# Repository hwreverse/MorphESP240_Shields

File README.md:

# MorphESP240 Shields
Here I will publish finished and "Work-in Progress" Shields Designs for the MorphESP 240 by [@ccadic](https://github.com/ccadic).
The MorphESP 240 is available after a successful campaign [here on Crowdsupply](https://www.crowdsupply.com/morpheans/morphesp-240). 

<br><br>
NB: I don't supply the firmware, I am busy with electronics :))

### - [Gamepad Shield 3D](https://github.com/hwreverse/MorphESP240_Shields/tree/main/mesp240_3Dpad) (complete)(UPDATED : 21.Aug.2021!)

- Next evolution of the Gamepad Shield in a new design with two additional analog josticks and a I2C Gyroscope + Accelerometer integrated circuit for Position & Inertia capture. 
- 2x4 Button Gamepad Shield and connection to optional Buzzer ready to be fabricated and assembled by the PCBA service of your choice. It can also be soldered by hand as I used only 0805 and SOT-23 footprints for the passives and the transistor (on the backside).  Pushbuttons are classic, comfy 12mm x 12mm x 4.3/5mm units, that won't use that much your fingertips. 
 
- <b>UPDATED: Moved all parts to front side. Changed strategy to factory assemby, therefore changed all passives to mainly 0402, at max 0603. Changed Accelerometer + Gyro to MPU6050, the Alps thumb joysticks to 3D161 from Korean Hroparts Elec (what was available @ JLCPCB/Parts for PCBA). 
- Removed the stupid 5V Connection. Added hardware debounce with RC-lowpass & Schmitt-Trigger on all buttons. 
- Added connection to +3.3V vibration motor. Added 2 LEDs Added 4 Pads (GND, +3.3V, SDA, SCL) on the backside of the PCB to be able to connect independently with the I2C BUS (gyro)
- Gerber files, BOM and CPL Files for Assembly (JLCPCB Format) and Project archive (Kicad 5.99 nightly only Format!) are available too. 

New Model:</b>

Old photos:

### - [Gamepad Shield](https://github.com/hwreverse/MorphESP240_Shields/tree/main/mesp240_gamepadshield) (complete)

- 2x4 Button Gamepad Shield and connection to optional Buzzer ready to be fabricated and assembled by the PCBA service of your choice. It can also be soldered by hand as I used only 0805 and SOT-23 footprints for the passives and the transistor (on the backside).  Pushbuttons are classic, comfy 12mm x 12mm x 4.3/5mm units, that won't use that much your fingertips. 
- Gerber files and archive are available too. I included alsoa BOM and a CPL file in the main Directory in the [JLCPCB](https://jlcpcb.com/) Format for PCBA (PCB Assembly)

### - [IRMaster Shield](https://github.com/hwreverse/MorphESP240_Shields/tree/main/mesp240_irmaster) (complete)

- Let's you control all IR controllable appliances: TV's, AC units, set top boxes,... Can learn any IR Code (What are IR Receiver and MorphESP-240 power good for!) 
Has also a special "TV–π–soff!" Button, with a functionality borrowed from TV-B-Gone, which turn off any known TV!
- Gerber files and archive are available too. 

### - [OPLL 8-bit Sound Card Shield](https://github.com/hwreverse/MorphESP240_Shields/tree/main/mesp240_opll) (complete)

- OPLL 8-Bit Sound Card Shield based on the cheap Yamaha YM2413B Sound Chip. As the MorphESP-240 only has 3.3V from the Lipo (5V only from USB), we had to generate 5V through a Boost converter for the YM2413B as well as the opamp. This implied that level conversion had to be added as well. Special care was exercised to get rid of the ripples for the 5V rail.
- Gerber files and archive are available too. 

### - [Da Bomb Shield (Draft - unfinished)](https://github.com/hwreverse/MorphESP240_Shields/tree/main/da_bomb_breadboard)

- If the project is great, then the Prototyping Shield must be surely...

**- Da Bomb!**

*... in the early design stage ...*

### - [MorphESP 240 to Sharp PC-G850* Shield](https://github.com/hwreverse/MorphESP240_Shields/tree/main/morphesp240_g850_interface) (complete)

- This shield offers an interface with bidirectiional level shifting form the 11pin Interface of Sharp Vintage Pocket Computers of the PC-G850 Series. (and any other Sharp with a 11pin Connector)<br>
- This Project is ready to be fabricated, a zip of the Gerber files is included.. As usual, I included alsoa BOM and a CPL file in the main Directory in the [JLCPCB](https://jlcpcb.com/) Format for PCBA (PCB Assembly), so you don't have to solder those pesky 0402 Resistors and capacitors 
<br>For more Pocketcomputer hardware see my other repositories [here](https://hwreverse.github.io/)

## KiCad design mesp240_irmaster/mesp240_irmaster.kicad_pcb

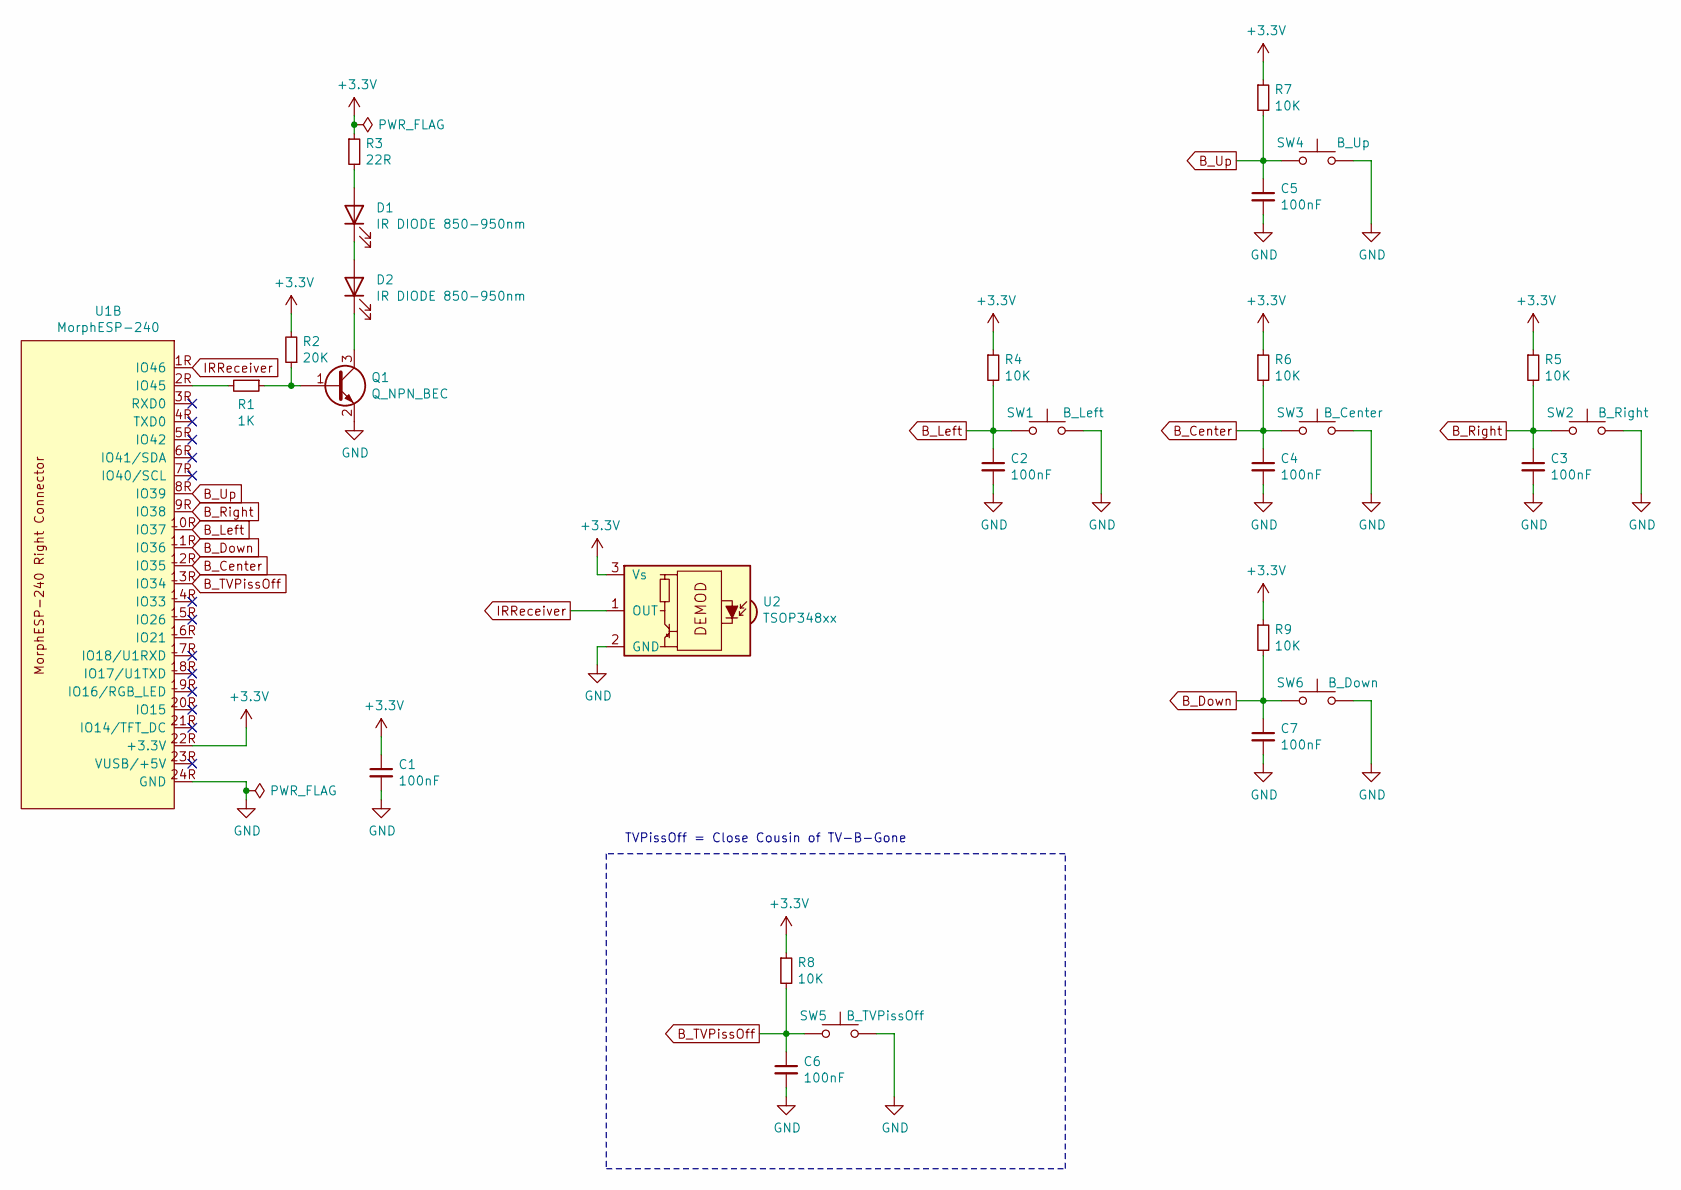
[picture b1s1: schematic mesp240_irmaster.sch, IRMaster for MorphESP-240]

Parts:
C1, C2, C3, C4, C5, C6, C7: 100nF; C_0805_2012Metric
D1: IR DIODE 850-950nm; LED_D5.0mm_IRBlack
D2: IR DIODE 850-950nm; LED_D5.0mm_IRGrey
Q1: Q_NPN_BEC; SOT-23
R1: 1K; R_0805_2012Metric_Pad1.20x1.40mm_HandSolder
R2: 20K; R_0805_2012Metric_Pad1.20x1.40mm_HandSolder
R3: 22R; R_0805_2012Metric_Pad1.20x1.40mm_HandSolder
R4, R5, R6, R7, R8, R9: 10K; R_0805_2012Metric_Pad1.20x1.40mm_HandSolder
SW1: B_Left; SW_PUSH_6mm_H4.3mm
SW2: B_Right; SW_PUSH_6mm_H4.3mm
SW3: B_Center; SW_PUSH_6mm_H4.3mm
SW4: B_Up; SW_PUSH_6mm_H4.3mm
SW5: B_TVPissOff; SW_PUSH_6mm_H4.3mm
SW6: B_Down; SW_PUSH_6mm_H4.3mm
U1: MorphESP-240; morphesp240
U2: TSOP348xx; Vishay_MOLD-3Pin

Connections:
+3V3: C1.1, R2.2, R3.1, R4.1, R5.1, R6.1, R7.1, R8.1, R9.1, U1.22R (+3.3V), U2.3 (Vs)
B_Center: C4.1, R6.2, SW3.1, U1.12R (IO35)
B_Down: C7.1, R9.2, SW6.1, U1.11R (IO36)
B_Left: C2.1, R4.2, SW1.1, U1.10R (IO37)
B_Right: C3.1, R5.2, SW2.1, U1.9R (IO38)
B_TVPissOff: C6.1, R8.2, SW5.1, U1.13R (IO34)
B_Up: C5.1, R7.2, SW4.1, U1.8R (IO39)
GND: C1.2, C2.2, C3.2, C4.2, C5.2, C6.2, C7.2, Q1.2 (E), SW1.2, SW2.2, SW3.2, SW4.2, SW5.2, SW6.2, U1.24R (GND), U2.2 (GND)
IRReceiver: U1.1R (IO46), U2.1 (OUT)
unnamed: D1.1 (K), D2.2 (A)
unnamed: D1.2 (A), R3.2
unnamed: D2.1 (K), Q1.3 (C)
unnamed: Q1.1 (B), R1.1, R2.1
unnamed: R1.2, U1.2R (IO45)

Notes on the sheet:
TVPissOff = Close Cousin of TV-B-Gone

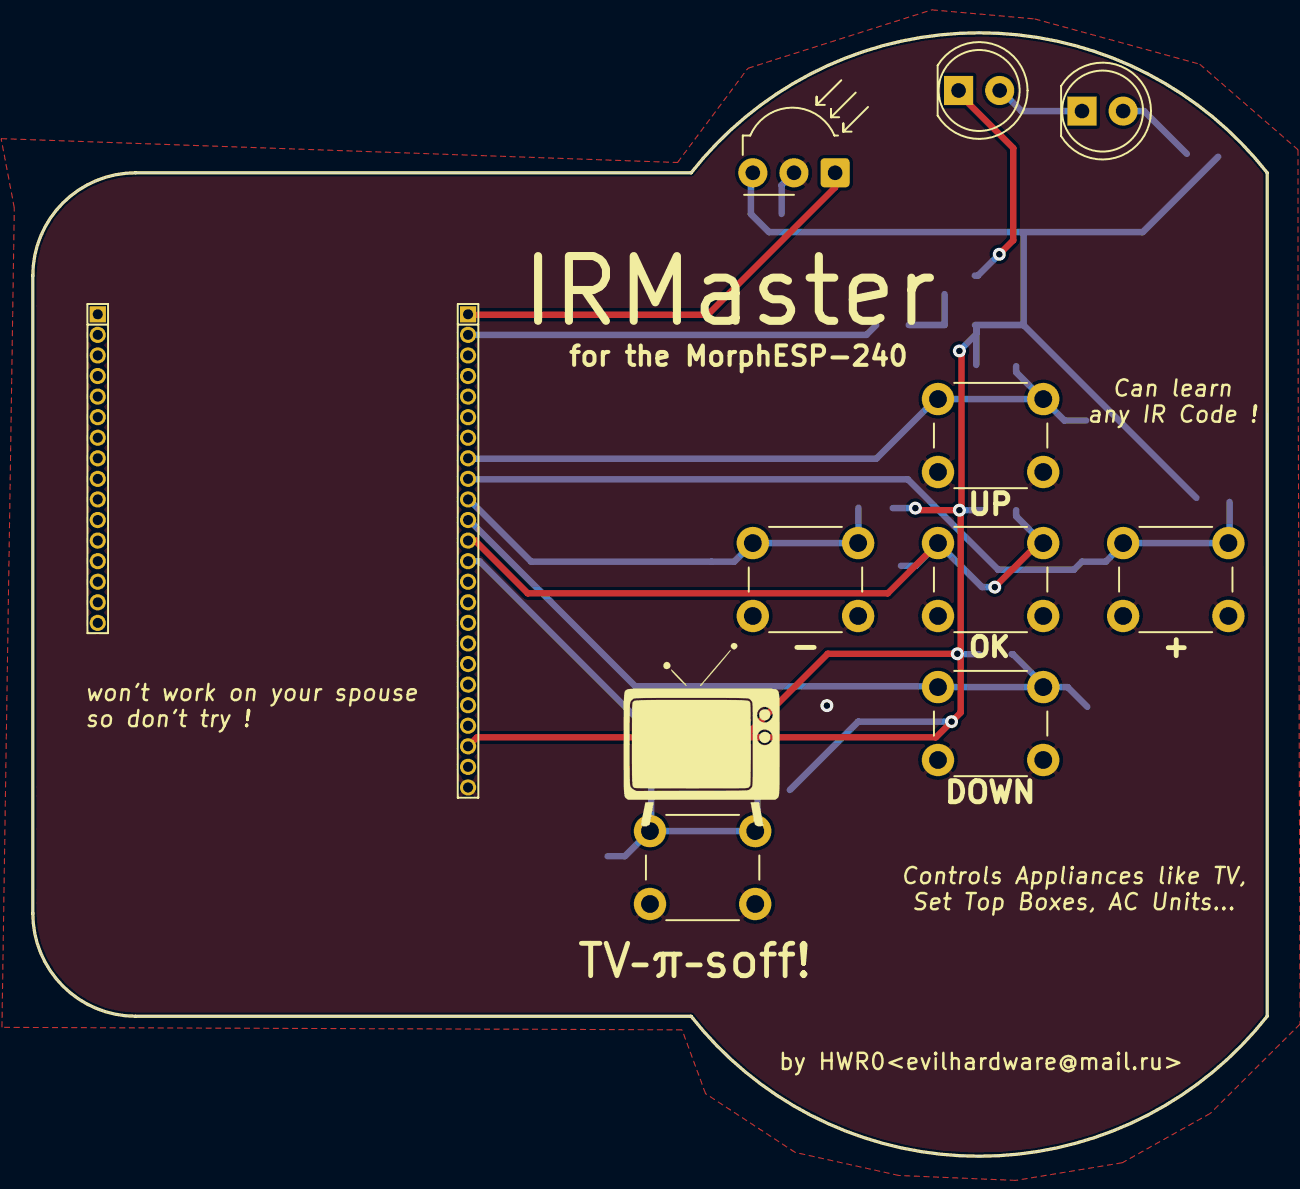
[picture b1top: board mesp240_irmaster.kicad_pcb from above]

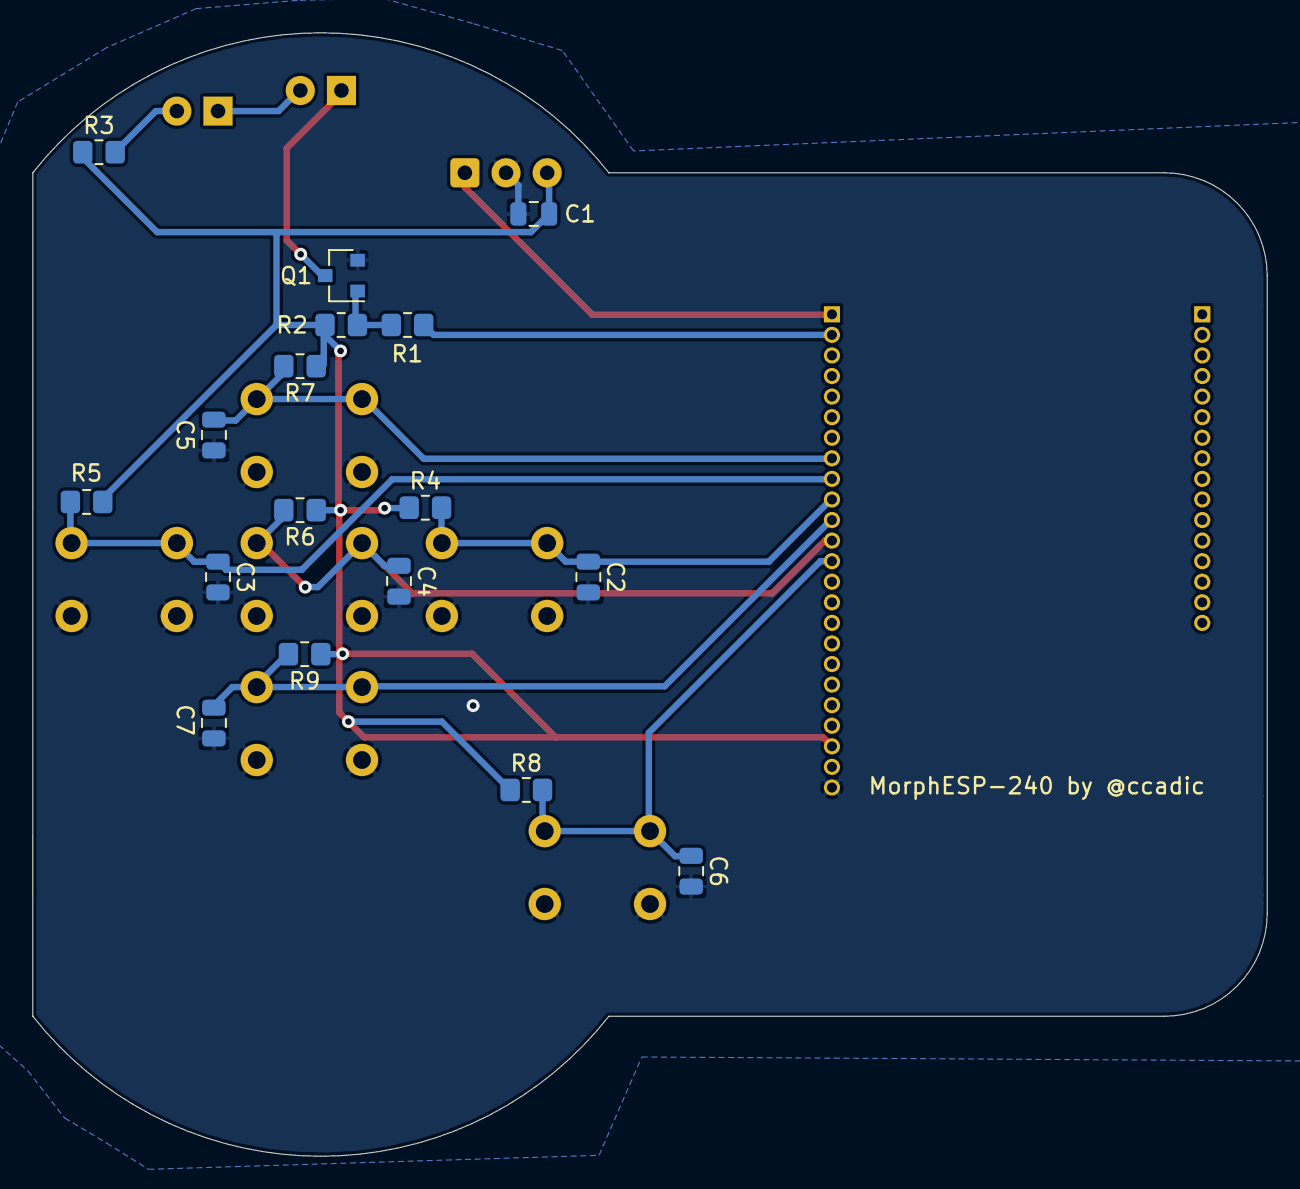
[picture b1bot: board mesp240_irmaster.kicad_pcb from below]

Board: 2 copper layers, 76.2 x 69.4 mm, 27 parts (17 on the bottom side), 14 nets.

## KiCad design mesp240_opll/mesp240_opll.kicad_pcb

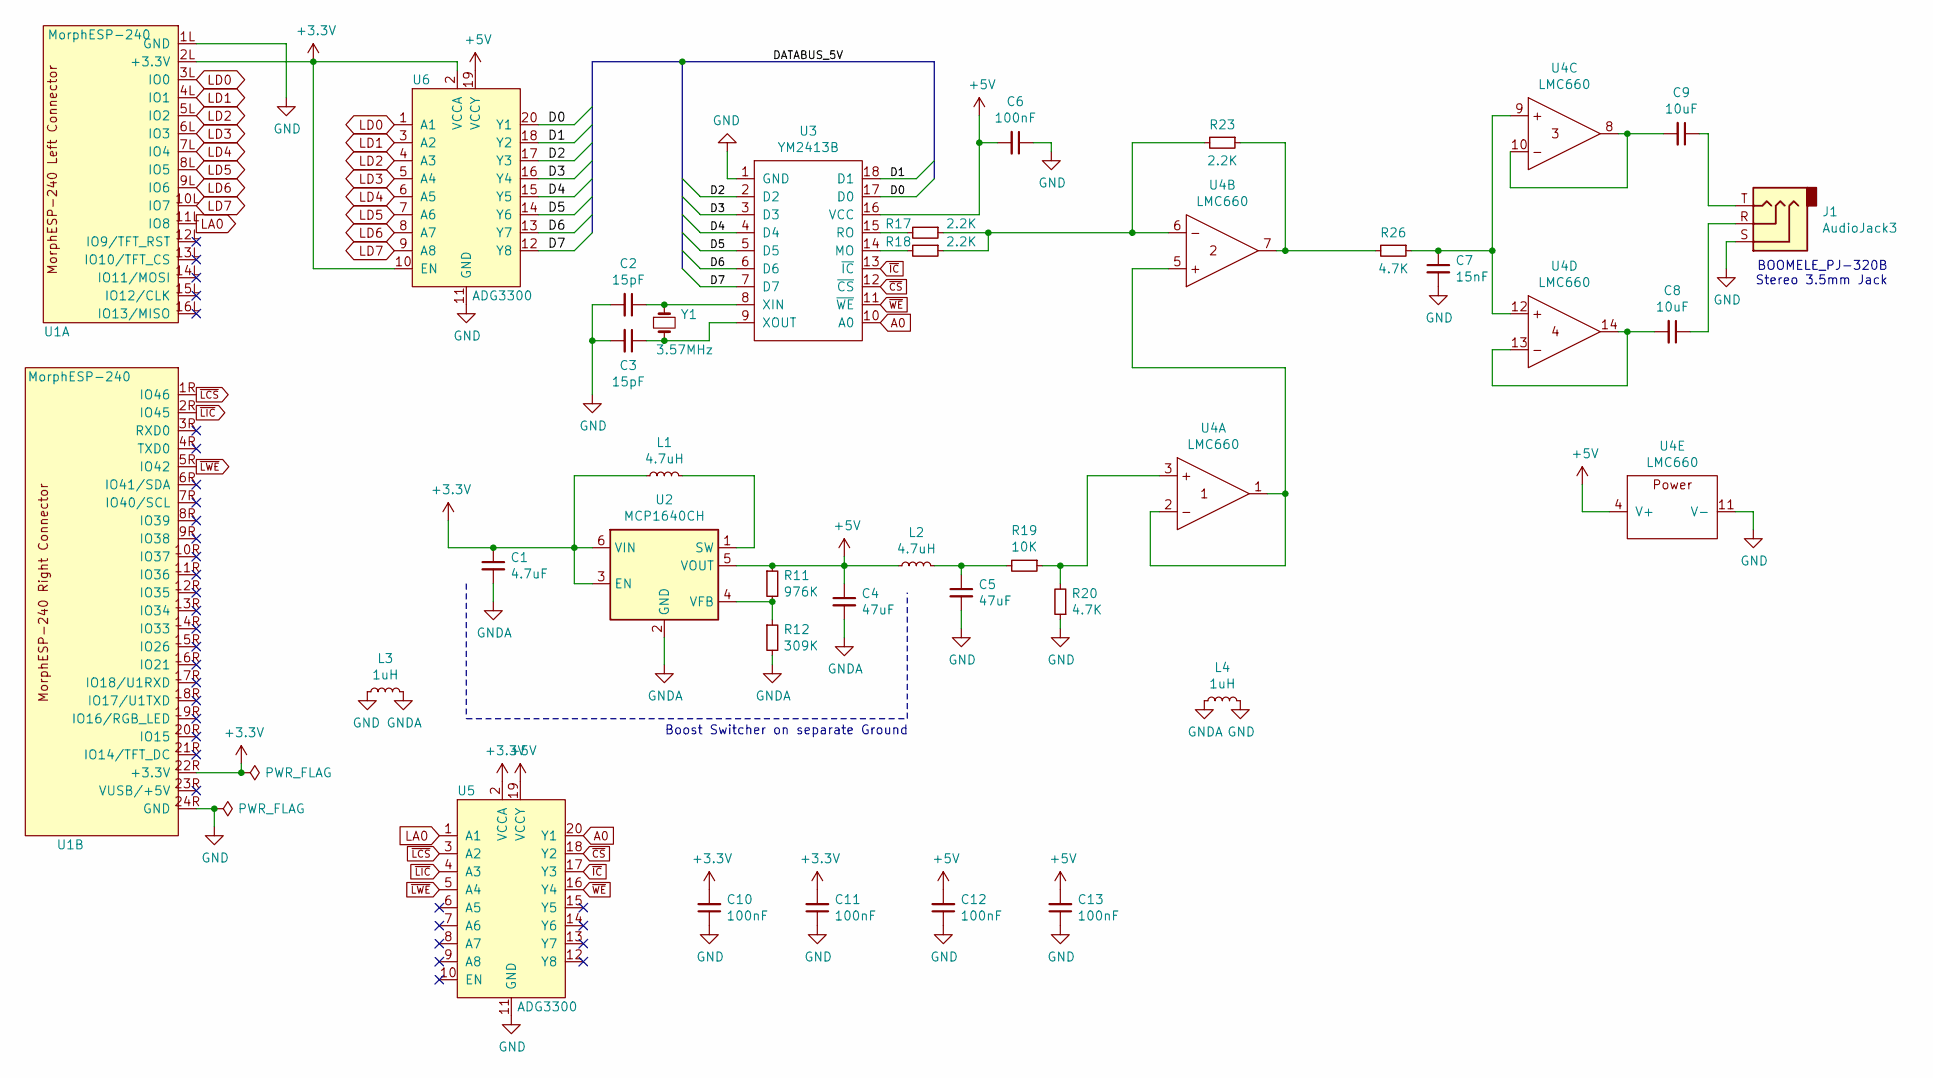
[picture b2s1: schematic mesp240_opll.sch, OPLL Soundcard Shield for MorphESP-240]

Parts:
C1: 4.7uF; C_0402_1005Metric
C2, C3: 15pF; C_0402_1005Metric
C4, C5: 47uF; C_1206_3216Metric_Pad1.33x1.80mm_HandSolder
C6, C10, C11, C12, C13: 100nF; C_0402_1005Metric
C7: 15nF; C_0402_1005Metric
C8, C9: 10uF; C_0805_2012Metric_Pad1.18x1.45mm_HandSolder
J1: AudioJack3; BOOMELE_PJ-320B
L1, L2: 4.7uH; C_1210_3225Metric_Pad1.33x2.70mm_HandSolder
L3, L4: 1uH; L_0805_2012Metric
R11: 976K; R_0402_1005Metric
R12: 309K; R_0402_1005Metric
R17, R18, R23: 2.2K; R_0603_1608Metric
R19: 10K; R_0603_1608Metric
R20, R26: 4.7K; R_0603_1608Metric
U1: MorphESP-240; morphesp240
U2: MCP1640CH; SOT-23-6
U3: YM2413B; DIP-18_W7.62mm
U4: LMC660; SOIC127P600X175-14N
U5, U6: ADG3300; TSSOP-20_4.4x6.5mm_P0.65mm
Y1: 3.57MHz; Crystal_SMD_3225-4Pin_3.2x2.5mm

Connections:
+3V3: C1.1, C10.2, C11.2, L1.1, U1.2L (+3.3V), U1.22R (+3.3V), U2.3 (EN), U2.6 (VIN), U5.2 (VCCA), U6.2 (VCCA), U6.10 (EN)
+5V: C4.1, C6.2, C12.2, C13.2, L2.1, R11.1, U2.5 (VOUT), U3.16 (VCC), U4.4 (V+), U5.19 (VCCY), U6.19 (VCCY)
/D0: U3.17 (D0), U6.20 (Y1)
/D1: U3.18 (D1), U6.18 (Y2)
/D2: U3.2 (D2), U6.17 (Y3)
/D3: U3.3 (D3), U6.16 (Y4)
/D4: U3.4 (D4), U6.15 (Y5)
/D5: U3.5 (D5), U6.14 (Y6)
/D6: U3.6 (D6), U6.13 (Y7)
/D7: U3.7 (D7), U6.12 (Y8)
A0: U3.10 (A0), U5.20 (Y1)
GND: C2.2, C3.2, C5.2, C6.1, C7.2, C10.1, C11.1, C12.1, C13.1, J1.S, L3.2, L4.2, R20.1, U1.1L (GND), U1.24R (GND), U3.1 (GND), U4.11 (V-), U5.11 (GND), U6.11 (GND)
GNDA: C1.2, C4.2, L3.1, L4.1, R12.2, U2.2 (GND)
LA0: U1.11L (IO8), U5.1 (A1)
LD0: U1.3L (IO0), U6.1 (A1)
LD1: U1.4L (IO1), U6.3 (A2)
LD2: U1.5L (IO2), U6.4 (A3)
LD3: U1.6L (IO3), U6.5 (A4)
LD4: U1.7L (IO4), U6.6 (A5)
LD5: U1.8L (IO5), U6.7 (A6)
LD6: U1.9L (IO6), U6.8 (A7)
LD7: U1.10L (IO7), U6.9 (A8)
unnamed: C2.1, U3.8 (XIN), Y1.1
unnamed: C3.1, U3.9 (XOUT), Y1.2
unnamed: C5.1, L2.2, R19.2
unnamed: C7.1, R26.1, U4.9, U4.12
unnamed: C8.1, J1.R
unnamed: C8.2, U4.13, U4.14
unnamed: C9.1, J1.T
unnamed: C9.2, U4.8, U4.10
unnamed: L1.2, U2.1 (SW)
unnamed: R11.2, R12.1, U2.4 (VFB)
unnamed: R17.1, R18.1, R23.2, U4.6
unnamed: R17.2, U3.15 (RO)
unnamed: R18.2, U3.14 (MO)
unnamed: R19.1, R20.2, U4.3
unnamed: R23.1, R26.2, U4.7
unnamed: U4.1, U4.2, U4.5
~CS: U3.12 (~CS), U5.18 (Y2)
~IC: U3.13 (~IC), U5.17 (Y3)
~LCS: U1.1R (IO46), U5.3 (A2)
~LIC: U1.2R (IO45), U5.4 (A3)
~LWE: U1.5R (IO42), U5.5 (A4)
~WE: U3.11 (~WE), U5.16 (Y4)

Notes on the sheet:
BOOMELE_PJ-320B Stereo 3.5mm Jack
Boost Switcher on separate Ground

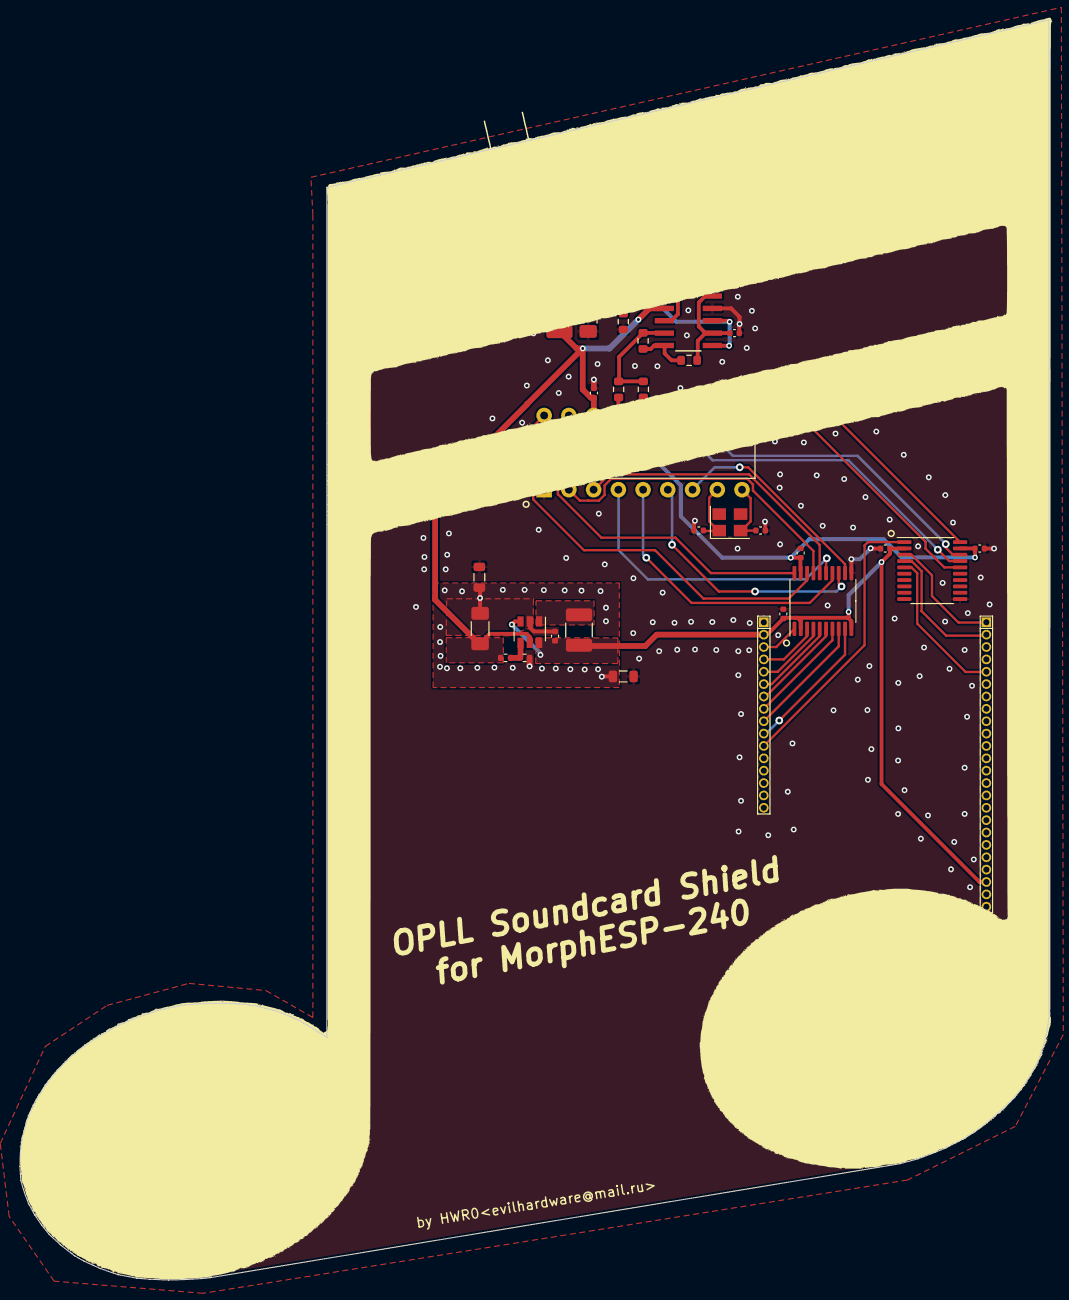
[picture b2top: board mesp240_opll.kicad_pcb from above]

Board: 2 copper layers, 105.7 x 129.4 mm, 33 parts (0 on the bottom side), 44 nets.

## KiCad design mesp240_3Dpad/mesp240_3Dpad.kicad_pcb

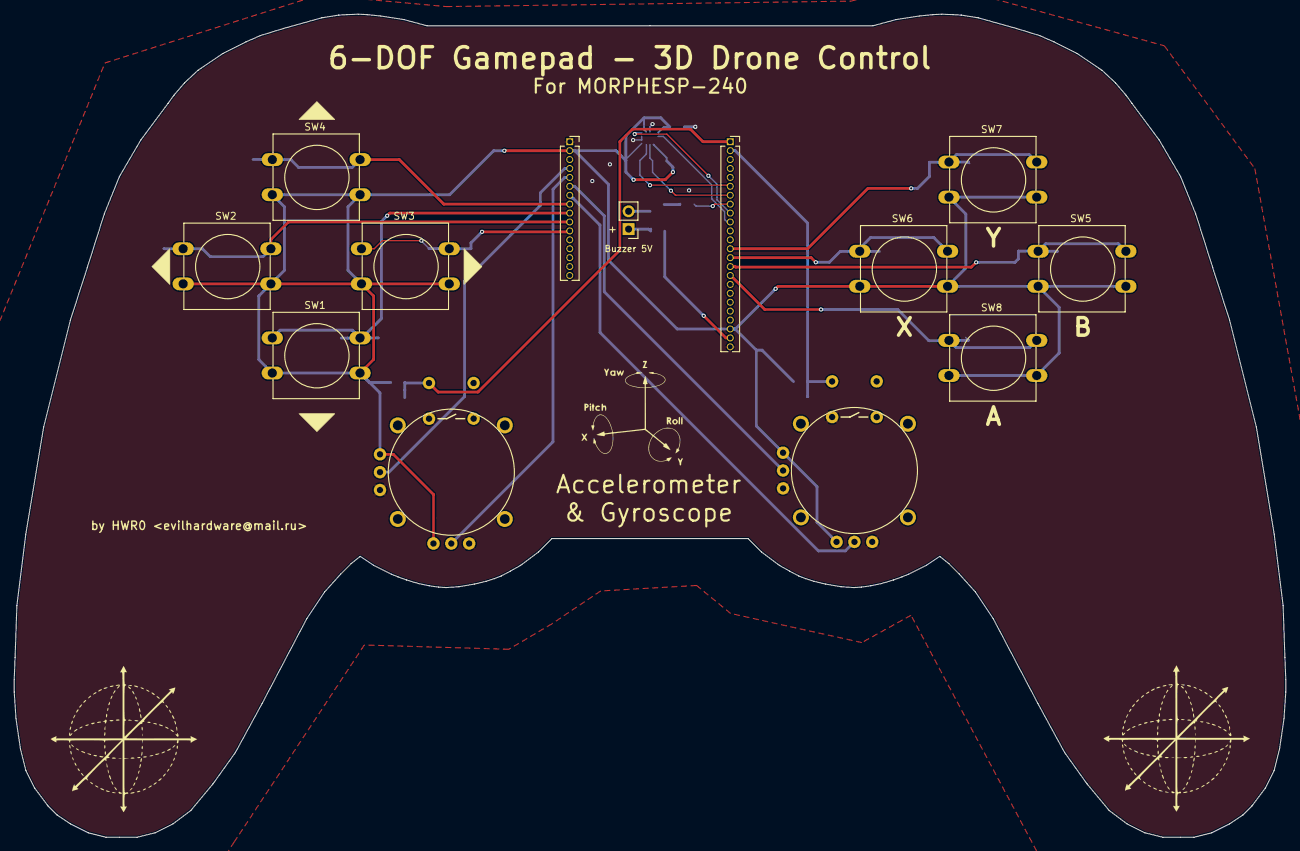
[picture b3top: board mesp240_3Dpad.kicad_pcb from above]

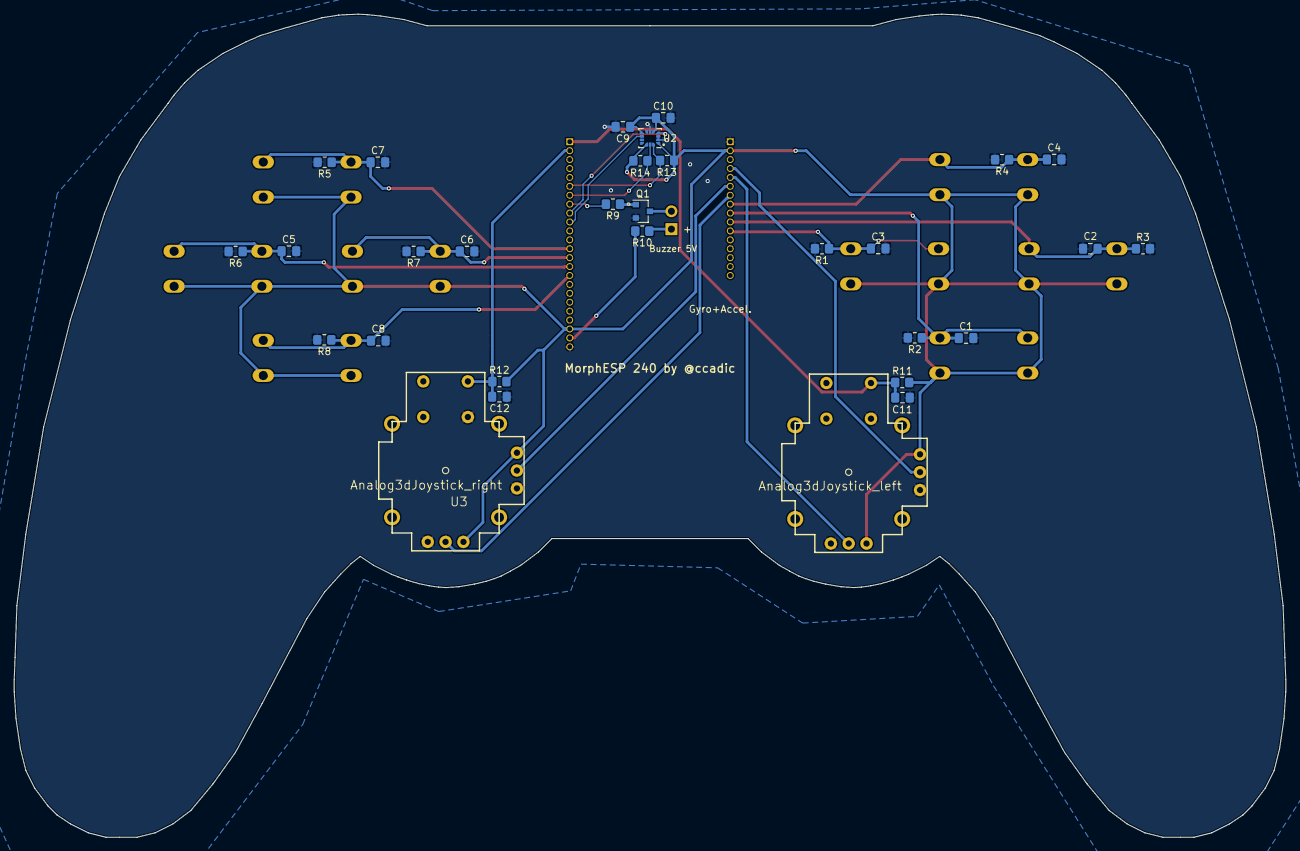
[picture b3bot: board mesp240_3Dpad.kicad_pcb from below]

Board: 2 copper layers, 181.1 x 117.2 mm, 41 parts (28 on the bottom side), 25 nets.

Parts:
C1, C2, C3, C4, C5, C6, C7, C8, C9, C10, C11, C12: 100nF; C_0805_2012Metric_Pad1.18x1.45mm_HandSolder
J1: 1.27P CNX; PinSocket_1x16_P1.27mm_Vertical
J2: 1.27P CNX; PinSocket_1x24_P1.27mm_Vertical
J3: Piezo Connector; PinHeader_1x02_P2.54mm_Vertical
Q1: MMBT3904; SOT-23
R1, R2, R3, R4, R5, R6, R7, R8, R11, R12: 10K; R_0805_2012Metric_Pad1.20x1.40mm_HandSolder
R9: 1K; R_0805_2012Metric_Pad1.20x1.40mm_HandSolder
R10: 100R; R_0805_2012Metric_Pad1.20x1.40mm_HandSolder
R13, R14: 4k7; R_0805_2012Metric_Pad1.20x1.40mm_HandSolder
SW1: Button DOWN; SW_PUSH-12mm
SW2: Button LEFT; SW_PUSH-12mm
SW3: Button Right; SW_PUSH-12mm
SW4: Button UP; SW_PUSH-12mm
SW5: Button B; SW_PUSH-12mm
SW6: Button X; SW_PUSH-12mm
SW7: Button Y; SW_PUSH-12mm
SW8: Button A; SW_PUSH-12mm
U1: Analog3dJoystick_left; JOYSTICK
U2: LSM6DS3; LGA-14_3x2.5mm_P0.5mm_LayoutBorder3x4y
U3: Analog3dJoystick_right; JOYSTICK

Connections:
/IO39: J2.8, R9.2
BUTTONA: C8.1, J2.16, R8.1, SW8.1
BUTTONB: C5.1, J2.15, R6.1, SW5.1
BUTTONJL: C11.1, J2.1, R11.2, U1.B1A
BUTTONJR: C12.1, J2.2, R12.2, U3.B1A
BUTTONX: C6.1, J2.14, R7.1, SW6.1
BUTTONY: C7.1, J2.13, R5.1, SW7.1
DOWN: C1.1, J1.9, R2.1, SW1.1
GND: C1.2, C2.2, C3.2, C4.2, C5.2, C6.2, C7.2, C8.2, C9.2, C10.2, C11.2, C12.2, J1.1, J2.24, Q1.2, R1.2, R2.2, R3.2, R4.2, R5.2, R6.2, R7.2, R8.2, U1.B2A, U1.H3, U1.V3, U2.2, U2.3, U2.6, U2.7, U3.B2A, U3.H3, U3.V3
HLEFT: J1.5, U1.H2
HRIGHT: J1.7, U3.H2
HV: J2.23, R10.2
INT1M6: J2.9, U2.4
INT2M6: J2.10, U2.9
LEFT: C2.1, J1.10, R3.1, SW2.1
LV: C9.1, C10.1, J1.2, J2.22, R11.1, R12.1, R13.1, R14.1, SW1.2, SW2.2, SW3.2, SW4.2, SW5.2, SW6.2, SW7.2, SW8.2, U1.H1, U1.V1, U2.1, U2.5, U2.8, U2.12, U3.H1, U3.V1
unnamed: J3.1, R10.1
unnamed: J3.2, Q1.3
unnamed: Q1.1, R9.1
RIGHT: C3.1, J1.11, R1.1, SW3.1
SCL: J2.7, R14.2, U2.13
SDA: J2.6, R13.2, U2.14
UP: C4.1, J1.8, R4.1, SW4.1
VLEFT: J1.4, U1.V2
VRIGHT: J1.6, U3.V2

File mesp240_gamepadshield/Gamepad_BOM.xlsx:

Comment | Designator | Footprint | LCSC
100nF | C1,C2,C3,C4,C5,C6,C7,C8 | Capacitor_SMD:C_0805_2012Metric_Pad1.18x1.45mm_HandSolder | C49678
1.27P CNX | J1 | Connector_PinSocket_1.27mm:PinSocket_1x16_P1.27mm_Vertical
1.27P CNX | J2 | Connector_PinSocket_1.27mm:PinSocket_1x24_P1.27mm_Vertical
Piezo Connector | J3 | Connector_PinHeader_2.54mm:PinHeader_1x02_P2.54mm_Vertical
MMBT3904 | Q1 | Package_TO_SOT_SMD:SOT-23 | C20526
100R | R10 | Resistor_SMD:R_0805_2012Metric_Pad1.20x1.40mm_HandSolder | C17408
10K | R1,R2,R3,R4,R5,R6,R7,R8 | Resistor_SMD:R_0805_2012Metric_Pad1.20x1.40mm_HandSolder | C17414
1K | R9 | Resistor_SMD:R_0805_2012Metric_Pad1.20x1.40mm_HandSolder | C17513
Button DOWN | SW1 | Button_Switch_THT:SW_PUSH-12mm | C620359
Button LEFT | SW2 | Button_Switch_THT:SW_PUSH-12mm | C620359
Button Right | SW3 | Button_Switch_THT:SW_PUSH-12mm | C620359
Button UP | SW4 | Button_Switch_THT:SW_PUSH-12mm | C620359
Button B | SW5 | Button_Switch_THT:SW_PUSH-12mm | C620359
Button X | SW6 | Button_Switch_THT:SW_PUSH-12mm | C620359
Button Y | SW7 | Button_Switch_THT:SW_PUSH-12mm | C620359
Button A | SW8 | Button_Switch_THT:SW_PUSH-12mm | C620359

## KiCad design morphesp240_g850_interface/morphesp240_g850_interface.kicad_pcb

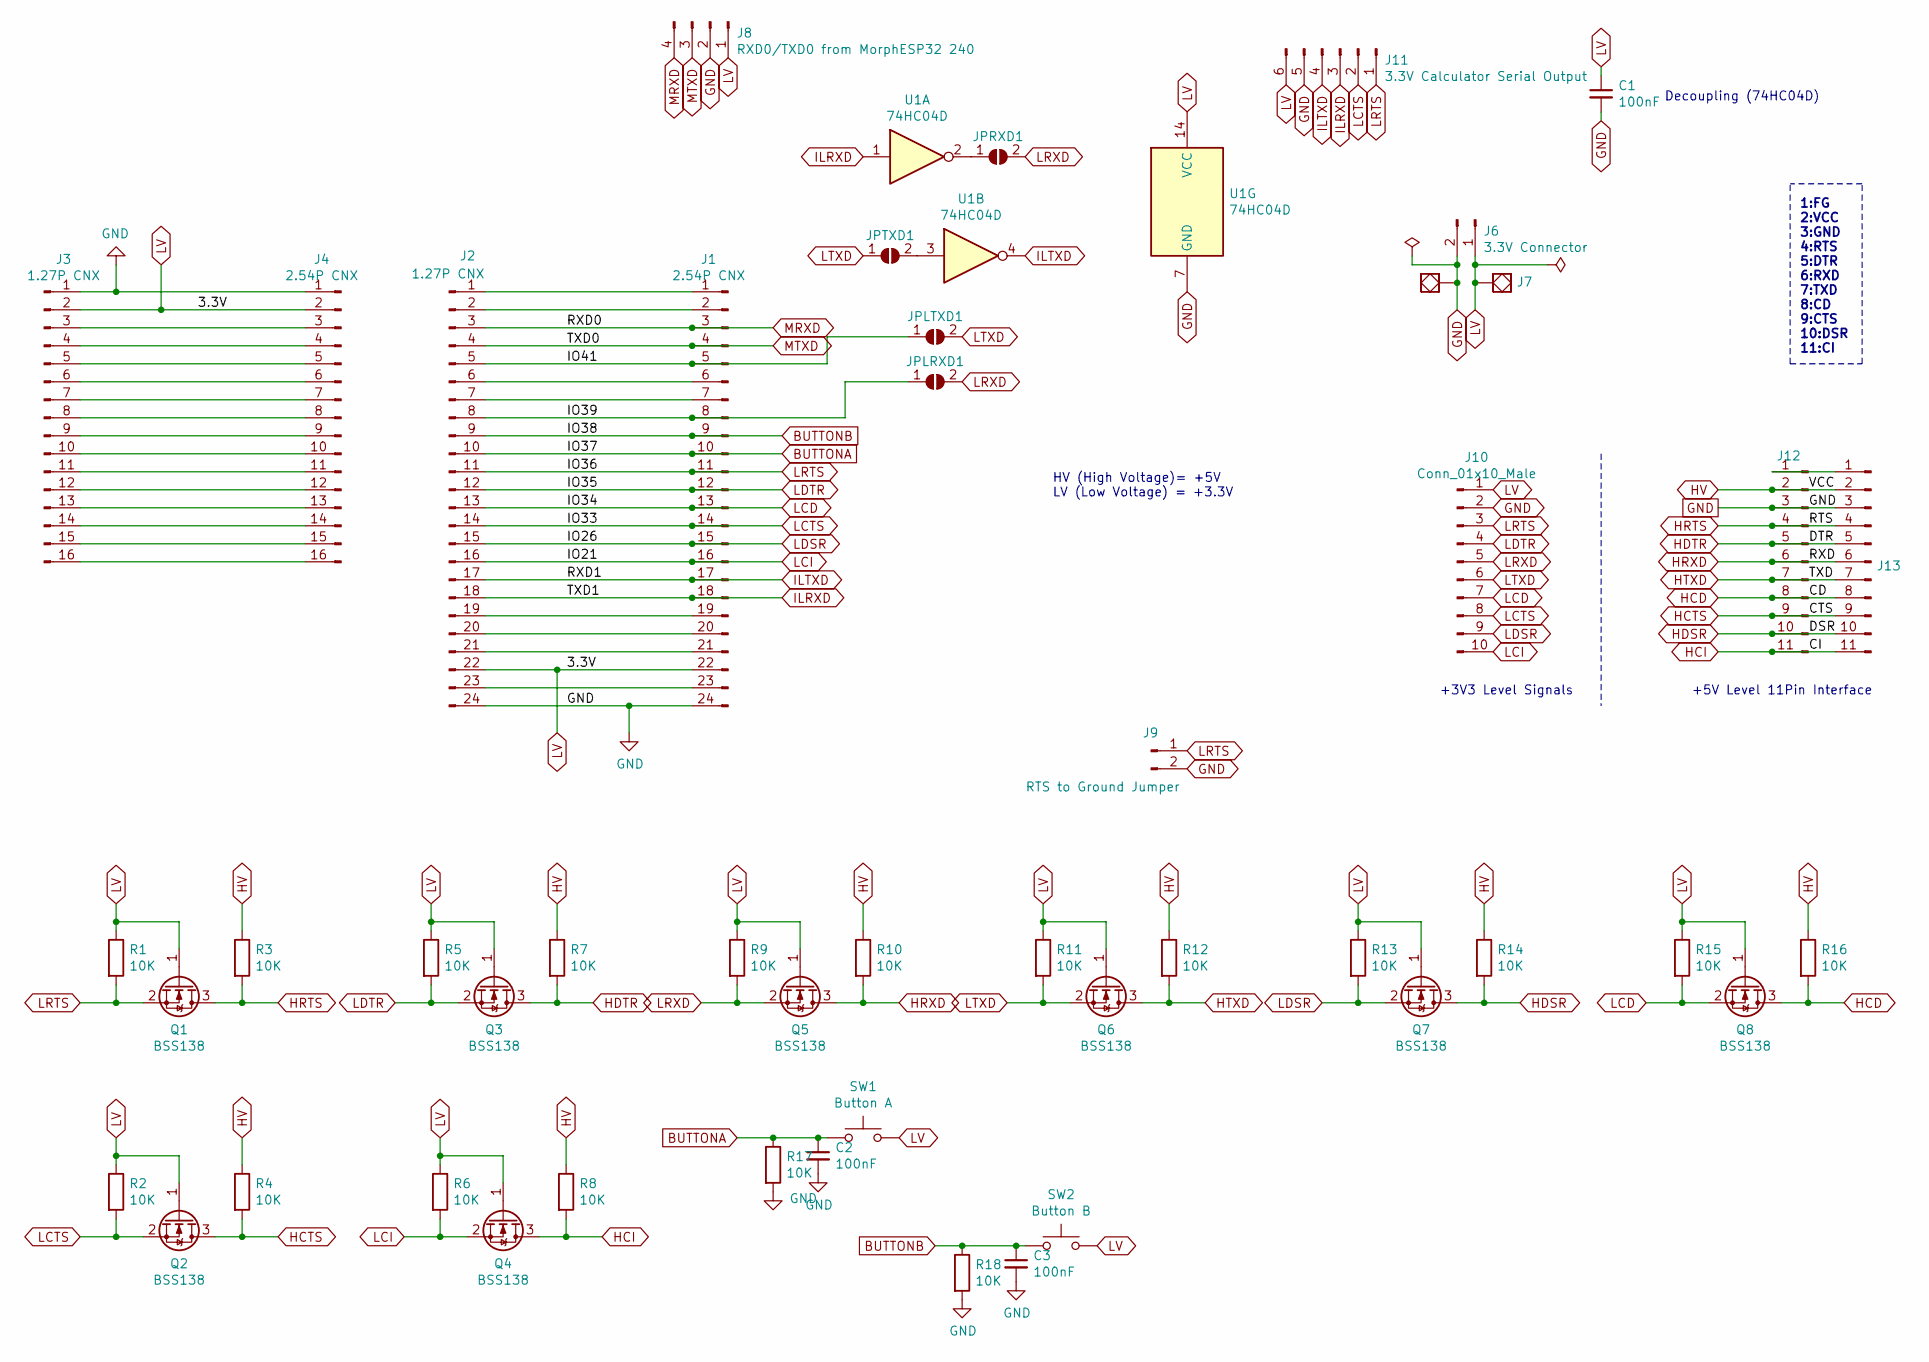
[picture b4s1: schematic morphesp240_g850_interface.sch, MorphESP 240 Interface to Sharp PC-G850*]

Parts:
C1, C2, C3: 100nF; C_0402_1005Metric; LCSC C1525
J1: 2.54P CNX; PinSocket_1x24_P2.54mm_Vertical
J2: 1.27P CNX; Socket_Strip_Straight_1x24_Pitch1.27mm
J3: 1.27P CNX; Socket_Strip_Straight_1x16_Pitch1.27mm
J4: 2.54P CNX; PinSocket_1x16_P2.54mm_Vertical
J5, J7: SolidPad-Connector; SolidPad_4x4mm_2x2mmCore
J6: 3.3V Connector; PinHeader_1x02_P2.54mm_Vertical
J8: RXD0/TXD0 from MorphESP32 240; PinHeader_1x04_P2.54mm_Vertical
J9: RTS to Ground Jumper; PinHeader_1x02_P2.54mm_Vertical
J10: Conn_01x10_Male; PinHeader_1x10_P2.54mm_Vertical
J11: 3.3V Calculator Serial Output; PinHeader_1x06_P2.54mm_Vertical
J12: CNDup; BreadBoard_2.54mm_1x11
J13: Conn_01x11_Male; PinHeader_1x11_P2.54mm_Horizontal
JPLRXD1: SolderJumper_2_Open; SolderJumper-2_P1.3mm_Open_RoundedPad1.0x1.5mm
JPLTXD1: SolderJumper_2_Open; SolderJumper-2_P1.3mm_Open_RoundedPad1.0x1.5mm
JPRXD1: SolderJumper_2_Open; SolderJumper-2_P1.3mm_Open_RoundedPad1.0x1.5mm
JPTXD1: SolderJumper_2_Open; SolderJumper-2_P1.3mm_Open_RoundedPad1.0x1.5mm
Q1, Q2, Q3, Q4, Q5, Q6, Q7, Q8: BSS138; SOT-23; LCSC C52895
R1, R2, R3, R4, R5, R6, R7, R8, R9, R10, R11, R12, R13, R14, R15, R16, R17, R18: 10K; R_0402_1005Metric; LCSC C25744
SW1: Button A; SW_PUSH-12mm; LCSC C620359
SW2: Button B; SW_PUSH-12mm; LCSC C620359
U1: 74HC04D; SOIC-14_3.9x8.7mm_P1.27mm; LCSC C5590

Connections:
/IO39: J1.8, J2.8, JPLRXD1.1 (A)
/IO41: J1.5, J2.5, JPLTXD1.1 (A)
BUTTONA: C2.1, J1.10, J2.10, R17.1, SW1.1
BUTTONB: C3.1, J1.9, J2.9, R18.1, SW2.1
GND: C1.2, C2.2, C3.2, J1.24, J2.24, J3.1, J4.1, J5.~, J6.2, J8.2, J9.2, J10.2, J11.5, J12.3, J13.3, R17.2, R18.2, U1.7 (GND)
HCD: J12.8, J13.8, Q8.3 (D), R16.2
HCI: J12.11, J13.11, Q4.3 (D), R8.2
HCTS: J12.9, J13.9, Q2.3 (D), R4.2
HDSR: J12.10, J13.10, Q7.3 (D), R14.2
HDTR: J12.5, J13.5, Q3.3 (D), R7.2
HRTS: J12.4, J13.4, Q1.3 (D), R3.2
HRXD: J12.6, J13.6, Q5.3 (D), R10.2
HTXD: J12.7, J13.7, Q6.3 (D), R12.2
HV: J12.2, J13.2, R3.1, R4.1, R7.1, R8.1, R10.1, R12.1, R14.1, R16.1
ILRXD: J1.18, J2.18, J11.3, U1.1
ILTXD: J1.17, J2.17, J11.4, U1.4
LCD: J1.13, J2.13, J10.7, Q8.2 (S), R15.2
LCI: J1.16, J2.16, J10.10, Q4.2 (S), R6.2
LCTS: J1.14, J2.14, J10.8, J11.2, Q2.2 (S), R2.2
LDSR: J1.15, J2.15, J10.9, Q7.2 (S), R13.2
LDTR: J1.12, J2.12, J10.4, Q3.2 (S), R5.2
LRTS: J1.11, J2.11, J9.1, J10.3, J11.1, Q1.2 (S), R1.2
LRXD: J10.5, JPLRXD1.2 (B), JPRXD1.2 (B), Q5.2 (S), R9.2
LTXD: J10.6, JPLTXD1.2 (B), JPTXD1.1 (A), Q6.2 (S), R11.2
LV: C1.1, J1.22, J2.22, J3.2, J4.2, J6.1, J7.~, J8.1, J10.1, J11.6, Q1.1 (G), Q2.1 (G), Q3.1 (G), Q4.1 (G), Q5.1 (G), Q6.1 (G), Q7.1 (G), Q8.1 (G), R1.1, R2.1, R5.1, R6.1, R9.1, R11.1, R13.1, R15.1, SW1.2, SW2.2, U1.14 (VCC)
MRXD: J1.3, J2.3, J8.4
MTXD: J1.4, J2.4, J8.3
unnamed: J1.1, J2.1
unnamed: J1.2, J2.2
unnamed: J1.6, J2.6
unnamed: J1.7, J2.7
unnamed: J1.19, J2.19
unnamed: J1.20, J2.20
unnamed: J1.21, J2.21
unnamed: J1.23, J2.23
unnamed: J3.3, J4.3
unnamed: J3.4, J4.4
unnamed: J3.5, J4.5
unnamed: J3.6, J4.6
unnamed: J3.7, J4.7
unnamed: J3.8, J4.8
unnamed: J3.9, J4.9
unnamed: J3.10, J4.10
unnamed: J3.11, J4.11
unnamed: J3.12, J4.12
unnamed: J3.13, J4.13
unnamed: J3.14, J4.14
unnamed: J3.15, J4.15
unnamed: J3.16, J4.16
unnamed: J12.1, J13.1
unnamed: JPRXD1.1 (A), U1.2
unnamed: JPTXD1.2 (B), U1.3

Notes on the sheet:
1:FG 2:VCC 3:GND 4:RTS 5:DTR 6:RXD 7:TXD 8:CD 9:CTS 10:DSR 11:CI
Decoupling (74HC04D)
+5V Level 11Pin Interface
+3V3 Level Signals
HV (High Voltage)= +5V LV (Low Voltage) = +3.3V
